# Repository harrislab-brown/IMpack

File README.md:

# IMpack

IMpack is a data logging IMU designed for research applications where sampling rate and compactness are paramount. The board costs less than $100 to fabricate and assemble and features an array of MEMS accelerometer chips which allow it to achieve a maximum acceleration measurement range of +/- 400 g, sampling rates up to 26.6 kHz and an angular rate measurement range of +/- 2000 deg/s. Compared to commercial options that use piezoresistive accelerometer elements and complicated analog frontends, the IMpack is very low cost while still achieving good signal-to-noise ratios via its highly selectable measurement range. The IMpack is 38 mm in diameter and approximately 13 mm thick including the single-cell LiPo battery which powers the device. The mass of the PCB itself is 5 grams; including the specified battery, the mass is 9 grams. The battery can be recharged using the micro USB port and the onboard charging circuitry. The microcontroller (STM32F4) gathers data from 3 high performance MEMS IMU chips and logs data to a micro SD card in a plain text CSV format. The parameters for recording including measurement range and sample rate are adjustable via a plain text settings file on the SD card which is used to configure the device on startup. An I2C expansion port allows the IMpack to interface with external sensors, or the synchronization of an array of IMpacks.

# Capabilities

The IMpack can be configured to sample data using any subset of the chips in its sensor array, including all of them at maximum sampling rate simultaneously. All of the chips used measure acceleration in three axes and the LSM6DSO32 contains a gyroscope as well. Sensor components with different strengths are chosen to improve the versatility of the device to different measurement situations. The MEMS IMU parts used and their primary specifications are listed in the following table.

| Sensor | Sample rate (kHz) | Bandwidth (kHz) | Range | Bit depth |
| :---: | :---: | :---: | :---: | :---: |
| IIS3DWB | 26.6 | 6.3 | +/- 16 g | 16 |
| LSM6DSO32 (accel.) | 6.66 | 3.33 | +/- 32 g | 16 |
| LSM6DSO32 (gyro.) | 6.66 | 1.44 | +/- 2000 deg/s | 16 |
| ADXL373 | 5.12 | 2.56 | +/- 400 g | 12 |

The frequency responses of each of 10 IMpack test units are shown in the plots below for data gathered from each IMU chip on the PCB. More details regarding the test setup are available in the accompanying publication (pre-print in the article directory). The raw testing data are available in the data directory.

# Bill of materials

| Description | Specification |
| :---: | :---: |
| Assembled IMpack PCB |  |
| Mounting fixture or enclosure | Examples in mechanical directory |
| Mounting screws | 4x M2 or #2 cap screws |
| Micro SD card | SanDisk Industrial 8 GB |
| LiPo battery | TinyCircuits ASR00003 |
| Adhesive rubber battery padding | McMaster-Carr 1374N13 |
| Programming cable | Tag-Connect TC2030 |
| Programmer | STLINK-V3MINIE |

# Instructions for use

This diagram illustrates the flow of operation of the IMpack. The red, orange and green LEDs are power indicators. The blue LED indicates the state of the device via its periodic blink sequence, where the width of each marker in the diagram indicates the duration of the blink and the light blue color indicates the LED is on. Once the device is powered up and initializes using the settings file on the SD card, pressing the button will begin and end a recording. Recordings can have a delayed start or acceleration trigger, or can stop after a predefined amount of time depending on the configuration as discussed in more detail later.   

## Programming the board

The IMpack is programmed via Serial Wire Debug using an [STLINK-V3MINIE](https://www.mouser.com/ProductDetail/STMicroelectronics/STLINK-V3MINIE?qs=MyNHzdoqoQKcLQe5Jawcgw%3D%3D&mgh=1&utm_id=17222215321&gad_source=1&gclid=Cj0KCQiA3sq6BhD2ARIsAJ8MRwUawTum9u1zJQP-2fxdKjuHkomzrG7uCrwYJbI-F8R0_4U0DyUifOMaAq6kEALw_wcB) debugger and a [Tag-Connect TC2030](https://www.tag-connect.com/product/tc2030-ctx-nl-stdc14-for-use-with-stm32-processors-with-stlink-v3) cable and [retaining clip](https://www.tag-connect.com/product/tc2030-retaining-clip-board-3-pack). We use [STM32CubeIDE](https://www.st.com/en/development-tools/stm32cubeide.html) to compile and launch the project. In the case of a failed flashing that results in an unresponsive microcontroller, the "boot" jumper on the top of the IMpack can be shorted at power up to initialize the microcontroller in boot mode and recover it.

## Charging the battery

The IMpack can be powered from any single-cell lithium polymer battery that can provide at least 150 mA of current and support a 100 mA charge rate. The battery connector is 2-pin JST-SH. We use a [150 mAh battery](https://tinycircuits.com/products/lithium-ion-polymer-battery-3-7v-150mah?srsltid=AfmBOopFKh3iH_07LgFVlMNDD-mnGZ0MBEidQ0zw9-TLOAf2Frq8NPOu) which provides approximately 2 hours of operation on a full charge. The battery polarity is indicated with silkscreen markings near the battery connector. Be sure that your battery matches since there seems to be some variation among different manufacturers.

The IMpack battery can be charged using the micro USB port with the power switch in either the on or off position. The red LED indicates that the IMpack is receiving power over USB. The IMpack can optionally be powered over USB only with no need for a battery. The orange and green LEDs indicate the charge status of the battery. While the USB is plugged in, the orange LED indicates that the battery is charging and the green LED turns on once the battery is fully charged. When operating the device without the USB plugged in, the orange LED will turn on once the battery voltage is low and it needs to be recharged.

## SD card

The IMpack logs data and reads in the recording parameters using a micro SD card. We use an [8 GB SanDisk Industrial](https://www.amazon.com/SanDisk-Industrial-MicroSDHC-SDSDQAF3-008G-I-Everything/dp/B085GL89HQ?th=1) card. The card should be formatted as FAT32. The IMpack will operate in the top-level directory of the card so it is recommended to use an empty card without any important data. 

The IMpack will likely work well with a variety of SD cards but an important factor to note is the write latency of the SD card. This specification is often provided as a generous upper bound so it is difficult to compare the real world performance of different SD cards based on their datasheets. If the real world write latency is too large, some IMU data can be lost during recording. In our testing the IMpack with SanDisk Industrial cards data loss is exceedingly rare.

## Taking a recording

With the IMpack connected to a power source (USB, battery or both), flip the power switch to the on position. The microcontroller will initialize the system and attempt to read in the settings file (more on that later). If the initialization is successful, the blue LED will blink twice. If no settings file is provided or the settings file is formatted incorrectly, the blue LED will blink 4 times. In this case the IMpack will write a correctly formatted default settings file to the card which can subsequently be tweaked by the user to configure the device. The blue LED should then begin flashing once every second, indicating that the device is in the idle state and ready to begin a recording. If instead there is a repeating sequence of 4 blinks, then the IMpack is in an error state (commonly due to a missing SD card).  

When the IMpack is idle, press the button to begin a recording. If a delay is configured, the device will enter the setup state where it waits before recording. A repeating sequence of 2 blue blinks indicates that the IMpack is in the setup state. After the configured delay, the device will enter the armed state if the recording is configured to begin based on an acceleration trigger. A repeating sequence of 3 blinks indicates that the IMpack is in the armed state. Once the acceleration trigger is detected, the device will begin recording, as indicated by rapid blinking of the blue LED. The recording will stop either after the configured recording length, or when the user presses the button again. After the recording, if data formatting is enabled, the device will spend some time formatting the raw sensor data into a plain text CSV file. A sequence of 3 slow blinks will indicate this state. Finally the device will return to the idle state at which point a new recording can be started or the device can be powered off. When the IMpack is not in use, the power switch should be in the off position to avoid draining the battery.

The recording sequence can be configured using the settings file and not all of the aforementioned states will necessarily be seen. For instance, if the delay before the armed state is set to zero and acceleration triggering is disabled, the device will immediately enter the recording state and begin logging data once the button is pressed. Similarly, the formatting state with 3 slow blinks will not be seen if data formatting is disabled, which may be desirable for long recordings at high data rates since the formatting can take a long time. In this case, the recording will be a binary file with the raw sensor data.

## Settings file

The settings.txt file on the SD card is used to configure the IMpack at startup. The sampling parameters for each IMU channel can be configured, as well as the overall recording parameters such as whether to wait for an acceleration trigger or whether to perform plain text formatting of the data file. An annotated example of the default settings file is shown below describing each of the parameters and their allowed values. If a valid settings file is not found on startup, the IMpack will generate a default one on the SD card - this is the recommended way to get started with the configuration.

```
LSM6DSx_accel_enabled = 1  # enable or disable each measurement channel with values 1 or 0
LSM6DSx_accel_odr_hz = 6660  # allowed values: 13, 26, 52, 104, 208, 416, 833, 1660, 3330, 6660
LSM6DSx_accel_range_g = 32  # allowed values: 4, 8, 16, 32
LSM6DSx_accel_lpf = 2  # setting for the low pass filter, 2 means bandwidth = ODR / 2 and so on (same meaning for other the other accelerometers), allowed values: 2, 4, 10, 20, 45, 100, 200, 400, 800
LSM6DSx_accel_offset_x_mg = 0  # these are DC offsets in milli-g, signed integer
LSM6DSx_accel_offset_y_mg = 0
LSM6DSx_accel_offset_z_mg = 0

LSM6DSx_gyro_enabled = 1
LSM6DSx_gyro_odr_hz = 6660  # allowed values: 13, 26, 52, 104, 208, 416, 833, 1660, 3330, 6660
LSM6DSx_gyro_range_dps = 2000  # allowed values: 125, 250, 500, 1000, 2000
LSM6DSx_gyro_lpf = 3  # this is the bit value that is put in the chip register, consult table 60 in LSM6DSO32 data sheet, allowed values: 0, 1, 2, 3, 4, 5, 6, 7

IIS3DWB_accel_enabled = 1
IIS3DWB_accel_range_g = 16  # allowed values: 2, 4, 8, 16
IIS3DWB_accel_lpf = 4  # allowed values: 4, 10, 20, 45, 100, 200, 400, 800
IIS3DWB_accel_offset_x_mg = 0
IIS3DWB_accel_offset_y_mg = 0
IIS3DWB_accel_offset_z_mg = 0

ADXL37x_accel_enabled = 1
ADXL37x_accel_odr_hz = 5120  # allowed values: 320, 640, 1280, 2560, 5120
ADXL37x_accel_lpf = 2  # allowed values: 2, 4, 8, 16, 32
ADXL37x_accel_offset_x_mg = 0
ADXL37x_accel_offset_y_mg = 0
ADXL37x_accel_offset_z_mg = 0

delay_before_armed_ms = 0  # how long to remain in the staging state in ms
recording_length_ms = 5000  # how long to record for in ms
data_formatting_enabled = 1  # if enabled, will create CSV files after each recording
accel_trigger_enabled = 0  # once armed, the recording will start based on an acceleration trigger if enabled
accel_trigger_on_any_axis = 0  # trigger if any axis exceeds the threshold if 1, else if 0 looks only for specific axis
accel_trigger_axis = 2  # 0, 1, 2 for x, y, z, axis selection to trigger from
accel_trigger_level_mg = 500  # level of the trigger in units of milli-g
accel_trigger_rising_edge = 0  # select whether to trigger on rising or falling edge
```

## Data format

When plain text data formatting is enabled, the IMpack will create a separate CSV file for each active channel from the recording. The columns for time stamps and axis measurements are labeled with units, so interpreting the file should be straightforward. The binary data files consist of sequences of data points which each consist of 12 bytes. Each data point contains the unsigned 32 bit time stamp in microseconds, 3 axes of signed 16 bit acceleration/angular rate data, and finally unsigned 16 bit data type tag to indicate which channel produced the data. Example scripts for parsing the binary data in MATLAB and Python are provided in the examples directory. 

# Hardware design

The board schematics, production files and KiCad 8 design files are available in the hardware directory. An enclosure or fixture is required to mount the IMpack depending on the application, which could be 3D printed or machined from metal in more stringent testing setups. Design files for the mechanical assemblies into which we mount the IMpack are available in the mechanical directory as examples. In our use case, we apply an adhesive rubber pad to the battery which allows it to be firmly clamped into the battery pocket as the IMpack mounting screws are tightened. The PCB is 4 layers with double sided assembly. The main components and their functions are listed below. A spreadsheet with all of the required components is available under hardware/production.

  - STM32F405 microcontroller (we use SDIO, SPI, NVIC, USB-FS, SWD, I2C hardware)
  - MCP73871 battery charge controller
  - TLV70033 LDO regulator
  - DM3D-SF micro SD card holder (most compact I could find)
  - IIS3DWB super high speed accelerometer with +/- 16 g range
  - ADXL373 high-g range accelerometer
  - LSM6DSO32 combined gyroscope and accelerometer with +/- 32 g range, low cost and widely available fallback option

We ordered 20 fully assembled IMpack units in calendar year 2024 to be manufactured by JLCPCB in batches of 5 or 10. The total cost per board ended up between 60 and 80 USD. A large contributor to the cost is the high performance accelerometer chips IIS3DWB and ADXL373 which typically cost 20 USD per chip in low quanitites. The board could be manufactured with the LSM6DSO32 as the only IMU chip, saving approximately 40 USD per unit, without otherwise compromising the functionality. 

# Firmware design

The source code for the IMpack is available as an STM32CubeIDE project in the firmware directory. The IMpack firmware is written in C and developed using the toolchain provided with STM32CubeIDE version 1.16.0 along with ST's Hardware Abstraction Layer library provided in the STM32Cube FW_F4 V1.28.1 firmware package. The IMpack firmware uses an interrupt based scheme to retrieve data from the IMU chips resulting in minimum latency in which the MCU listens to the data ready pin from each chip and initiates the SPI data read on the appropriate edges of the data pin signal. The SPI read subroutine uses direct register manipulation for improved speed. Each data packet is tagged with a time stamp and an identifier for which chip it came from and inserted into a large double buffer in RAM. The buffer is written to a file on the SD card in binary format periodically as each half of the buffer is filled. Finally, at the end of the recording, the binary data file is read back and converted into a CSV text file on the SD card for more convenient processing by the user. A big challenge is the SD card write latency (up to 250 ms latency according to the data sheet for the SanDisk Industrial card used). Data from the IMU chips needs to be double buffered so we can put new data from the sensors in one half while the other half is being written to the file. This means we would have to store 500 ms worth of data in memory to guarantee no data loss. At such high data rates, this is not feasible without using additional memory chips or a larger MCU. In practice, the actual latency of the SD card we selected is much lower so we don't lose data, but this is something to be aware of if a different SD card is used. Data loss can be easily detected by calculating the interval between successive data point time stamps and comparing with the expected sampling period based on the configuration.

# License

IMpack is licensed under the CC BY-SA 4.0 Creative Commons license.

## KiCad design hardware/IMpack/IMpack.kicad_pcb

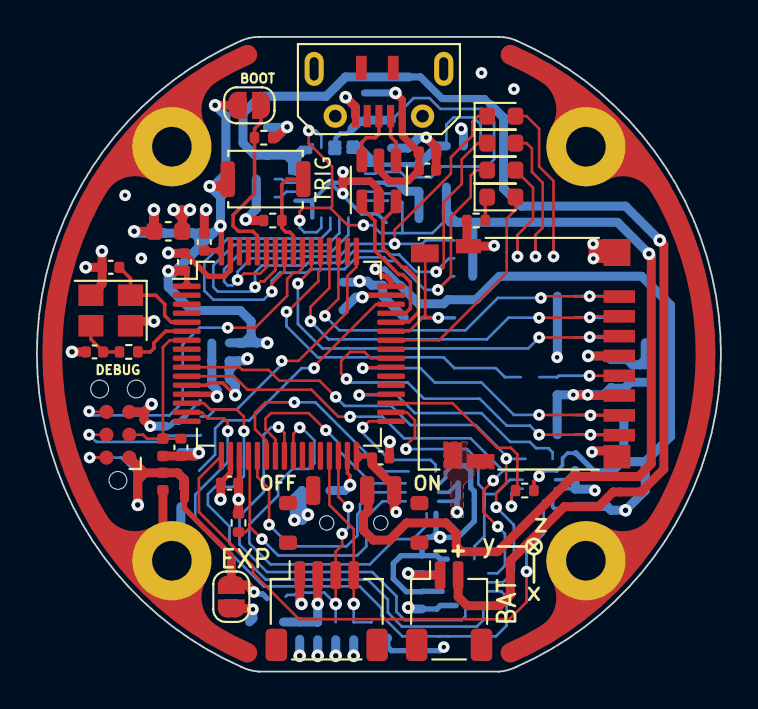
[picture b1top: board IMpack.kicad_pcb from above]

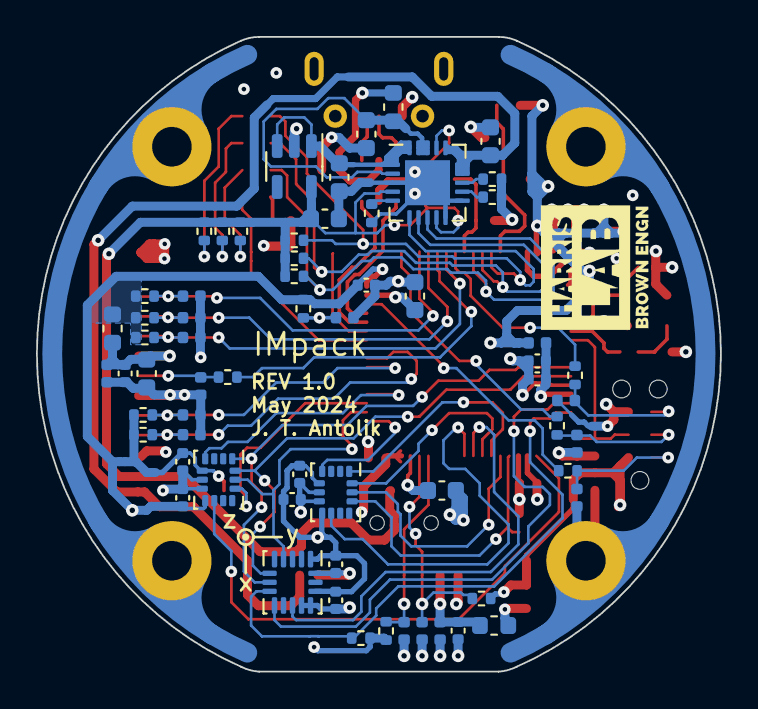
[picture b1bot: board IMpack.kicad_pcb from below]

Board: 4 copper layers, 38.0 x 35.3 mm, 105 parts (65 on the bottom side), 65 nets.

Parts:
C201, C301, C501: 10u; C_0603_1608Metric
C202, C203, C204: 4u7; C_0603_1608Metric
C302, C304, C306, C307, C308, C312, C401, C502, C601, C602, C603, C604, C605, C606, C701: 100n; C_0402_1005Metric
C303, C305: 2u2; C_0603_1608Metric
C309: 1u; C_0402_1005Metric
C310: 10n; C_0402_1005Metric
C311, C313: 12p; C_0402_1005Metric
D201: RED; LED_0603_1608Metric
D202: ORANGE; LED_0603_1608Metric
D203: GREEN; LED_0603_1608Metric
D301: BLUE; LED_0603_1608Metric
D302, D303, D304, D305, D306, D401, D501, D502, D503, D504, D505, D506, D507, D508, D701, D702, D703: RCLAMP0521P-N; D_0402_1005Metric
FB201, FB501, FB701: 100R; L_0603_1608Metric
H701, H702, H703, H704: MountingHole_Pad; MountingHole_2.2mm_M2_Pad
J201: JST_SH_BAT; JST_SH_SM02B-SRSS-TB_1x02-1MP_P1.00mm_Horizontal
J301: TagConnect_TC2030-NL; Tag-Connect_TC2030-IDC-NL_2x03_P1.27mm_Vertical
J401: USB_B_Micro; MicroXNJ
J501: DM3D-SF; microSD_HC_Hirose_DM3D-SF
J701: JST_SH_EXPANSION; JST_SH_SM04B-SRSS-TB_1x04-1MP_P1.00mm_Horizontal
JP301: BOOT0; SolderJumper-2_P1.3mm_Open_RoundedPad1.0x1.5mm
JP701: 3.3V; SolderJumper-2_P1.3mm_Open_RoundedPad1.0x1.5mm
L301: 39n; L_0402_1005Metric
N701, N702, N703, N704: Housing_Pad; Board_Outline
R201, R203, R204, R205, R206, R302, R303, R701, R702: 10k; R_0402_1005Metric
R202: 100k; R_0402_1005Metric
R207, R208, R301: 1k5; R_0402_1005Metric
R209: 510; R_0402_1005Metric
R304: 47; R_0402_1005Metric
R305, R306, R307, R501: 22; R_0402_1005Metric
R502, R503, R504, R505, R506, R507, R601, R602, R603: 47k; R_0402_1005Metric
SW201: SW_ON_OFF; MSS12C02LS-BB2.0
SW301: BUTTON; SW_Push_SPST_NO_Alps_SKRK
U201: MCP73871; QFN-20-1EP_4x4mm_P0.5mm_EP2.5x2.5mm
U202: TLV70033_SOT23-5; SOT-23-5
U301: STM32F405RGT6; LQFP-64_10x10mm_P0.5mm
U401: USBLC6-2SC6; SOT-23-6
U601: LSM6DSO32TR; LGA-14_3x2.5mm_P0.5mm_LayoutBorder3x4y
U602: ADXL37x; Analog_LGA-16_3.25x3mm_P0.5mm_LayoutBorder3x5y
U603: IIS3DWBTR; LGA-14_3x2.5mm_P0.5mm_LayoutBorder3x4y
Y301: 16MHz; Crystal_SMD_3225-4Pin_3.2x2.5mm

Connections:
+3.3V: C301.1, C302.1, C304.1, C306.1, C307.1, C308.1, C601.1, C602.1, C603.1, C604.1, C605.1, C606.1, D302.1 (A1), FB501.1, J301.1 (VCC), JP301.2 (B), JP701.1 (A), L301.1, R502.1, R503.1, R504.1, R505.1, R506.1, R507.1, R601.1, R602.1, R603.1, R701.1, R702.1, SW201.3 (C), SW301.2, U301.1 (VBAT), U301.19 (VDD), U301.32 (VDD), U301.48 (VDD), U301.64 (VDD), U601.5 (VDDIO), U601.8 (VDD), U602.1 (V_{DD_I/O}), U602.14 (V_{S}), U603.5 (VDDIO), U603.8 (VDD)
+3.3VA: C309.1, C310.1, L301.2, U301.13 (VDDA)
+5V: C401.1, D401.1 (A1), FB201.1, J401.1 (VBUS), U401.5 (VBUS)
/Microcontroller/SWD_SWCLK_PRT: D304.1 (A1), J301.4 (SWCLK), R305.2
/Microcontroller/SWD_SWDIO_PRT: D305.1 (A1), J301.2 (SWDIO), R306.2
/Microcontroller/SWD_SWO_PRT: D306.1 (A1), J301.6 (SWO), R307.2
/Power/BCM_PROG1: R201.2, U201.13 (PROG1)
/Power/BCM_PROG3: R202.2, U201.12 (PROG3)
/Power/BCM_THERM: R203.2, U201.5 (THERM)
/Power/BCM_VBAT: C204.1, J201.2, U201.14 (V_{BAT}), U201.15 (V_{BAT}), U201.16 (V_{BAT_SENSE})
ADXL37x_INT1: U301.24 (PC4), U602.11 (INT1)
ADXL37x_INT2: U301.14 (PA0), U602.9 (INT2)
ADXL37x_NSS: R602.2, U301.15 (PA1), U602.8 (~CS)
BCM_IN: C201.1, FB201.2, U201.2 (VPCC), U201.18 (IN), U201.19 (IN)
BCM_OUT: C202.1, U201.1 (OUT), U201.20 (OUT), U202.1 (IN), U202.3 (EN)
BCM_PG: D201.1 (K), R206.2, U201.6 (~PG), U301.59 (PB7)
BCM_STAT1: D202.1 (K), R205.2, U201.8 (STAT1/~LBO), U301.57 (PB5)
BCM_STAT2: D203.1 (K), R204.2, U201.7 (STAT2), U301.58 (PB6)
BOOT0: JP301.1 (A), R303.1, U301.60 (BOOT0)
BUTTON: R302.1, SW301.1, U301.56 (PB4)
GND: C201.2, C202.2, C203.2, C204.2, C301.2, C302.2, C303.2, C304.2, C305.2, C306.2, C307.2, C308.2, C309.2, C310.2, C311.2, C312.2, C313.2, C401.2, C501.2, C502.2, C601.2, C602.2, C603.2, C604.2, C605.2, C606.2, C701.2, D302.2 (A2), D303.2 (A2), D304.2 (A2), D305.2 (A2), D306.2 (A2), D401.2 (A2), D501.2 (A2), D502.2 (A2), D503.2 (A2), D504.2 (A2), D505.2 (A2), D506.2 (A2), D507.2 (A2), D508.2 (A2), D701.2 (A2), D702.2 (A2), D703.2 (A2), H701.1, H702.1, H703.1, H704.1, J201.1, J301.5 (GND), J401.5 (GND), J501.6 (VSS), J501.9 (DET_B), J501.11 (SHIELD), J701.1, N701.1 (PAD), N702.1 (PAD), N703.1 (PAD), N704.1 (PAD), R201.1, R202.1, R203.1, R301.2, R302.2, R303.2, U201.3 (SEL), U201.10 (V_{SS}), U201.11 (V_{SS}), U201.21 (V_{SS}), U202.2 (GND), U301.12 (VSSA), U301.18 (VSS), U301.63 (VSS), U401.2 (GND), U601.6 (GND), U601.7 (GND), U602.12 (GND), U602.13 (GND), U602.16 (GND), U603.6 (GND), U603.7 (GND), Y301.2, Y301.4
HSE_IN: C311.1, U301.5 (PH0), Y301.1
HSE_OUT: R304.1, U301.6 (PH1)
I2C2_SCL: D703.1 (A1), J701.4, R702.2, U301.29 (PB10)
I2C2_SDA: D702.1 (A1), J701.3, R701.2, U301.30 (PB11)
IIS3DWB_INT1: U301.36 (PB15), U603.4 (INT1)
IIS3DWB_INT2: U301.17 (PA3), U603.9 (INT2)
IIS3DWB_NSS: R603.2, U301.35 (PB14), U603.12 (CS)
LED_STATUS: D301.2 (A), U301.42 (PA9)
LSM6DSx_INT1: U301.33 (PB12), U601.4 (INT1)
LSM6DSx_INT2: U301.25 (PC5), U601.9 (INT2)
unnamed: C313.1, R304.2, Y301.3
unnamed: D201.2 (A), R207.1
unnamed: D202.2 (A), R208.1
unnamed: D203.2 (A), R209.1
unnamed: D301.1 (K), R301.1
unnamed: D504.1 (A1), J501.5 (CLK), R501.1
unnamed: C501.1, C502.1, D506.1 (A1), FB501.2, J501.4 (VDD)
unnamed: C701.1, D701.1 (A1), FB701.2, J701.2
unnamed: FB701.1, JP701.2 (B)
unnamed: C303.1, U301.31 (VCAP_1)
unnamed: C305.1, U301.47 (VCAP_2)
REG_OUT: C203.1, R204.1, R205.1, R206.1, R207.2, R208.2, R209.2, SW201.2 (B), U201.4 (PROG2), U201.9 (~TE), U201.17 (CE), U202.5 (OUT)
SD_CARD_DETECT: D501.1 (A1), J501.10 (DET_A), R502.2, U301.43 (PA10)
SD_SDIO_CLK: R501.2, U301.53 (PC12)
SD_SDIO_CMD: D505.1 (A1), J501.3 (CMD), R505.2, U301.54 (PD2)
SD_SDIO_D0: D503.1 (A1), J501.7 (DAT0), R504.2, U301.39 (PC8)
SD_SDIO_D1: D502.1 (A1), J501.8 (DAT1), R503.2, U301.40 (PC9)
SD_SDIO_D2: D508.1 (A1), J501.1 (DAT2), R507.2, U301.51 (PC10)
SD_SDIO_D3: D507.1 (A1), J501.2 (DAT3/CD), R506.2, U301.52 (PC11)
SPI1_MISO: U301.22 (PA6), U601.1 (SDO/SA0)
SPI1_MOSI: U301.23 (PA7), U601.14 (SDA)
SPI1_NSS: R601.2, U301.20 (PA4), U601.12 (CS)
SPI1_SCLK: U301.21 (PA5), U601.13 (SCL)
SPI2_MISO: U301.10 (PC2), U602.7 (MISO), U603.1 (SDO/SA0)
SPI2_MOSI: U301.11 (PC3), U602.6 (MOSI), U603.14 (SDA)
SPI2_SCLK: U301.34 (PB13), U602.4 (SCLK), U603.13 (SCL)
SWD_NRST: C312.1, D303.1 (A1), J301.3 (~RESET), U301.7 (NRST)
SWD_SWCLK: R305.1, U301.49 (PA14)
SWD_SWDIO: R306.1, U301.46 (PA13)
SWD_SWO: R307.1, U301.55 (PB3)
USB_CONN_D+: J401.3 (D+), U401.6 (I/O1)
USB_CONN_D-: J401.2 (D-), U401.4 (I/O2)
USB_D+: U301.45 (PA12), U401.1 (I/O1)
USB_D-: U301.44 (PA11), U401.3 (I/O2)

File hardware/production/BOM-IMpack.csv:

Comment,Designator,Footprint,LCSC,Quantity
100R,"FB201,FB501,FB701",L_0603_1608Metric,C1002,3
TLV70033_SOT23-5,U202,SOT-23-5,C11337,1
16MHz,Y301,Crystal_SMD_3225-4Pin_3.2x2.5mm,C13738,1
10n,C310,C_0402_1005Metric,C15195,1
100n,"C302,C304,C306,C307,C308,C312,C401,C502,C601,C602,C603,C604,C605,C606,C701",C_0402_1005Metric,C1525,15
12p,"C311,C313",C_0402_1005Metric,C1547,2
STM32F405RGT6,U301,LQFP-64_10x10mm_P0.5mm,C15742,1
JST_SH_BAT,J201,JST_SH_SM02B-SRSS-TB_1x02-1MP_P1.00mm_Horizontal,C160402,1
JST_SH_EXPANSION,J701,JST_SH_SM04B-SRSS-TB_1x04-1MP_P1.00mm_Horizontal,C160404,1
LSM6DSO32TR,U601,LGA-14_3x2.5mm_P0.5mm_LayoutBorder3x4y,C1864162,1
4u7,"C202,C203,C204",C_0603_1608Metric,C19666,3
10u,"C201,C301,C501",C_0603_1608Metric,C19702,3
BUTTON,SW301,SW_Push_SPST_NO_Alps_SKRK,C202388,1
RED,D201,LED_0603_1608Metric,C2286,1
2u2,"C303,C305",C_0603_1608Metric,C23630,2
22,"R305,R306,R307,R501",R_0402_1005Metric,C25092,4
47,R304,R_0402_1005Metric,C25118,1
510,R209,R_0402_1005Metric,C25123,1
100k,R202,R_0402_1005Metric,C25741,1
10k,"R201,R203,R204,R205,R206,R302,R303,R701,R702",R_0402_1005Metric,C25744,9
47k,"R502,R503,R504,R505,R506,R507,R601,R602,R603",R_0402_1005Metric,C25792,9
1k5,"R207,R208,R301",R_0402_1005Metric,C25867,3
39n,L301,L_0402_1005Metric,C26443,1
USBLC6-2SC6,U401,SOT-23-6,C2827654,1
SW_ON_OFF,SW201,MSS12C02LS-BB2.0,C3008585,1
RCLAMP0521P-N,"D302,D303,D304,D305,D306,D401,D501,D502,D503,D504,D505,D506,D507,D508,D701,D702,D703",D_0402_1005Metric,C316043,17
ADXL37x,U602,Analog_LGA-16_3.25x3mm_P0.5mm_LayoutBorder3x5y,C3216386,1
USB_B_Micro,J401,MicroXNJ,C404969,1
MCP73871,U201,QFN-20-1EP_4x4mm_P0.5mm_EP2.5x2.5mm,C511310,1
1u,C309,C_0402_1005Metric,C52923,1
IIS3DWBTR,U603,LGA-14_3x2.5mm_P0.5mm_LayoutBorder3x4y,C717702,1
DM3D-SF,J501,microSD_HC_Hirose_DM3D-SF,C719027,1
GREEN,D203,LED_0603_1608Metric,C84264,1
BLUE,D301,LED_0603_1608Metric,C84266,1
ORANGE,D202,LED_0603_1608Metric,C84269,1

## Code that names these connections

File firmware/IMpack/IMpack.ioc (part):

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Mcu.Name=STM32F405RGTx
Mcu.Package=LQFP64
Mcu.UserName=STM32F405RGTx
PA0-WKUP.GPIOParameters=GPIO_Label
PA0-WKUP.GPIO_Label=ADXL37x_INT2
PA0-WKUP.Signal=GPXTI0
PA1.GPIOParameters=GPIO_Speed,PinState,GPIO_Label
PA1.GPIO_Label=ADXL37x_NSS
PA1.GPIO_Speed=GPIO_SPEED_FREQ_VERY_HIGH
PA1.PinState=GPIO_PIN_SET
PA1.Signal=GPIO_Output
PA10.GPIOParameters=GPIO_Label
PA10.GPIO_Label=SD_CARD_DETECT
PA10.Signal=GPIO_Input
PA11.Mode=Device_Only
PA11.Signal=USB_OTG_FS_DM
PA12.Mode=Device_Only
PA12.Signal=USB_OTG_FS_DP
PA13.Mode=Trace_Asynchronous_SW
PA13.Signal=SYS_JTMS-SWDIO
PA14.Mode=Trace_Asynchronous_SW
PA14.Signal=SYS_JTCK-SWCLK
PA3.GPIOParameters=GPIO_Label
PA3.GPIO_Label=IIS3DWB_INT2
PA3.Signal=GPXTI3
PA4.GPIOParameters=GPIO_Speed,PinState,GPIO_Label
PA4.GPIO_Label=SPI1_NSS
PA4.GPIO_Speed=GPIO_SPEED_FREQ_VERY_HIGH
PA4.PinState=GPIO_PIN_SET
PA4.Signal=GPIO_Output
PA5.Mode=Full_Duplex_Master
PA5.Signal=SPI1_SCK
PA6.Mode=Full_Duplex_Master
PA6.Signal=SPI1_MISO
PA7.Mode=Full_Duplex_Master
PA7.Signal=SPI1_MOSI
PA9.GPIOParameters=PinState,GPIO_Label
PA9.GPIO_Label=LED_STATUS
PA9.PinState=GPIO_PIN_RESET
PA9.Signal=GPIO_Output
PB10.GPIOParameters=GPIO_Pu
PB10.GPIO_Pu=GPIO_NOPULL
PB10.Mode=I2C
PB10.Signal=I2C2_SCL
PB11.GPIOParameters=GPIO_Pu
PB11.GPIO_Pu=GPIO_NOPULL
PB11.Mode=I2C
PB11.Signal=I2C2_SDA
PB12.GPIOParameters=GPIO_Label
PB12.GPIO_Label=LSM6DSx_INT1
PB12.Signal=GPXTI12
PB13.Mode=Full_Duplex_Master
PB13.Signal=SPI2_SCK
PB14.GPIOParameters=GPIO_Speed,PinState,GPIO_Label
PB14.GPIO_Label=IIS3DWB_NSS
PB14.GPIO_Speed=GPIO_SPEED_FREQ_VERY_HIGH
PB14.PinState=GPIO_PIN_SET
PB14.Signal=GPIO_Output
PB15.GPIOParameters=GPIO_Label
PB15.GPIO_Label=IIS3DWB_INT1
PB15.Signal=GPXTI15
PB3.Mode=Trace_Asynchronous_SW
PB3.Signal=SYS_JTDO-SWO
PB4.GPIOParameters=GPIO_Label
PB4.GPIO_Label=BUTTON
PB4.Signal=GPIO_Input
PC10.Signal=SDIO_D2
PC11.Signal=SDIO_D3
PC12.GPIOParameters=GPIO_PuPd
PC12.GPIO_PuPd=GPIO_NOPULL
PC12.Mode=SD_1_bit
PC12.Signal=SDIO_CK
PC2.Mode=Full_Duplex_Master
PC2.Signal=SPI2_MISO
PC3.Mode=Full_Duplex_Master
PC3.Signal=SPI2_MOSI
PC4.GPIOParameters=GPIO_Label
PC4.GPIO_Label=ADXL37x_INT1
PC4.Signal=GPXTI4
PC5.GPIOParameters=GPIO_Label
PC5.GPIO_Label=LSM6DSx_INT2
PC5.Signal=GPXTI5
PC8.GPIOParameters=GPIO_PuPd
PC8.GPIO_PuPd=GPIO_NOPULL
PC8.Mode=SD_1_bit
PC8.Signal=SDIO_D0
PC9.Signal=SDIO_D1
PD2.GPIOParameters=GPIO_PuPd
PD2.GPIO_PuPd=GPIO_NOPULL
PD2.Mode=SD_1_bit
PD2.Signal=SDIO_CMD
PH0-OSC_IN.Mode=HSE-External-Oscillator
PH0-OSC_IN.Signal=RCC_OSC_IN
PH1-OSC_OUT.Mode=HSE-External-Oscillator
PH1-OSC_OUT.Signal=RCC_OSC_OUT
RCC.HSE_VALUE=16000000
RCC.SYSCLKFreq_VALUE=168000000
RCC.SYSCLKSource=RCC_SYSCLKSOURCE_PLLCLK
board=custom

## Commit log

2024-12-05 added board files
2024-12-05 misc
2024-12-05 added board production files
2024-12-05 added firmware
2025-03-07 added readme assets
2025-03-07 added water entry data and frequency response scripts
2025-03-07 added mechanical designs
2025-03-11 added license
2025-03-11 rename schematic
